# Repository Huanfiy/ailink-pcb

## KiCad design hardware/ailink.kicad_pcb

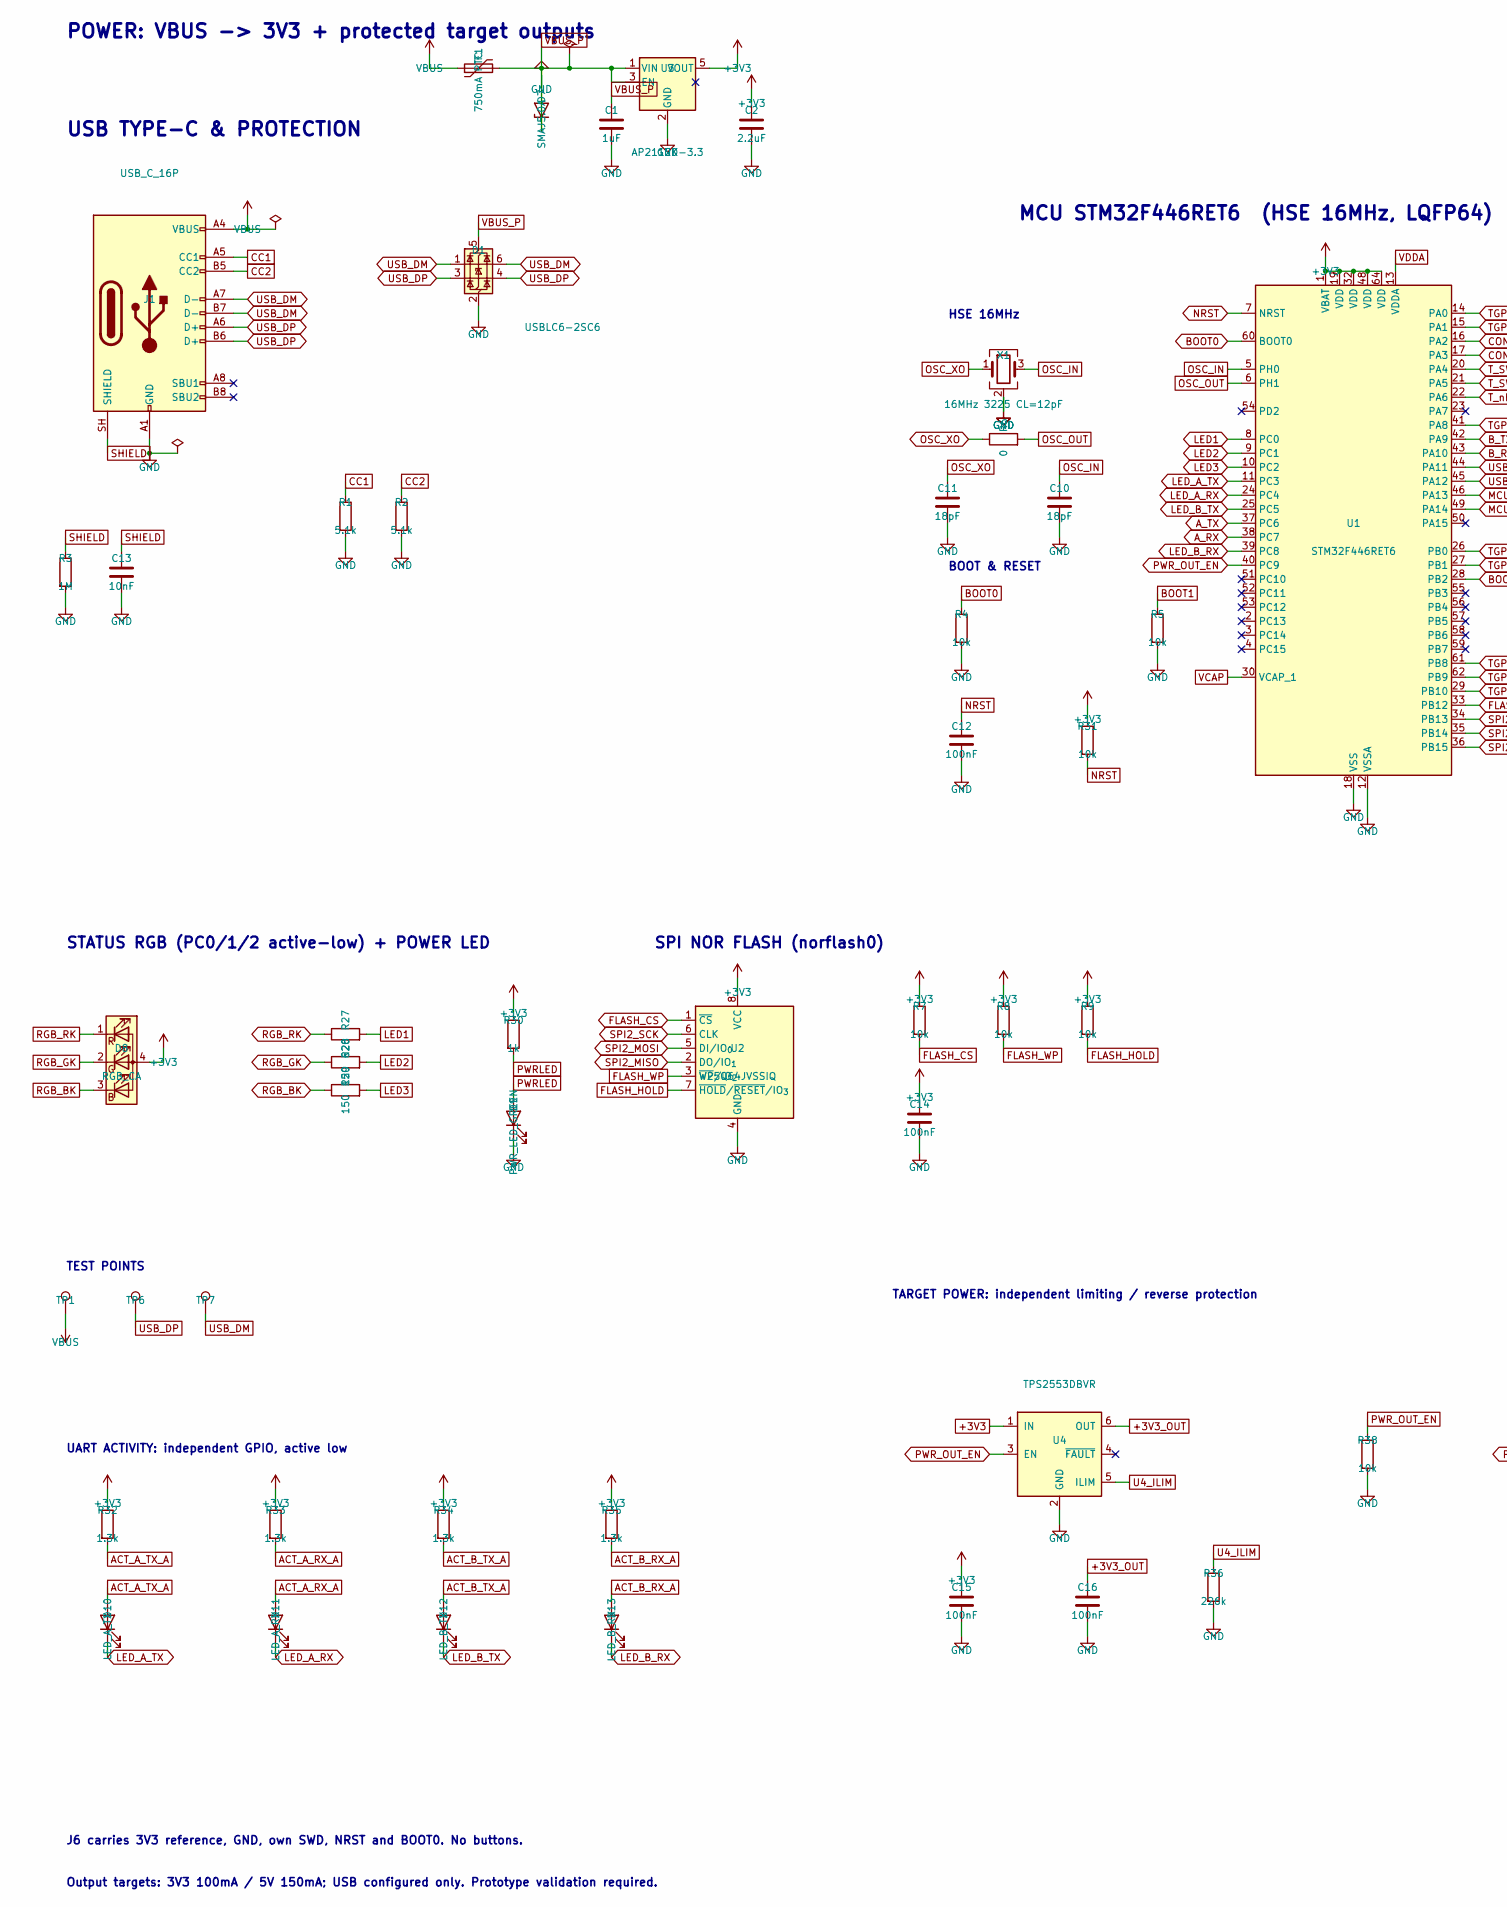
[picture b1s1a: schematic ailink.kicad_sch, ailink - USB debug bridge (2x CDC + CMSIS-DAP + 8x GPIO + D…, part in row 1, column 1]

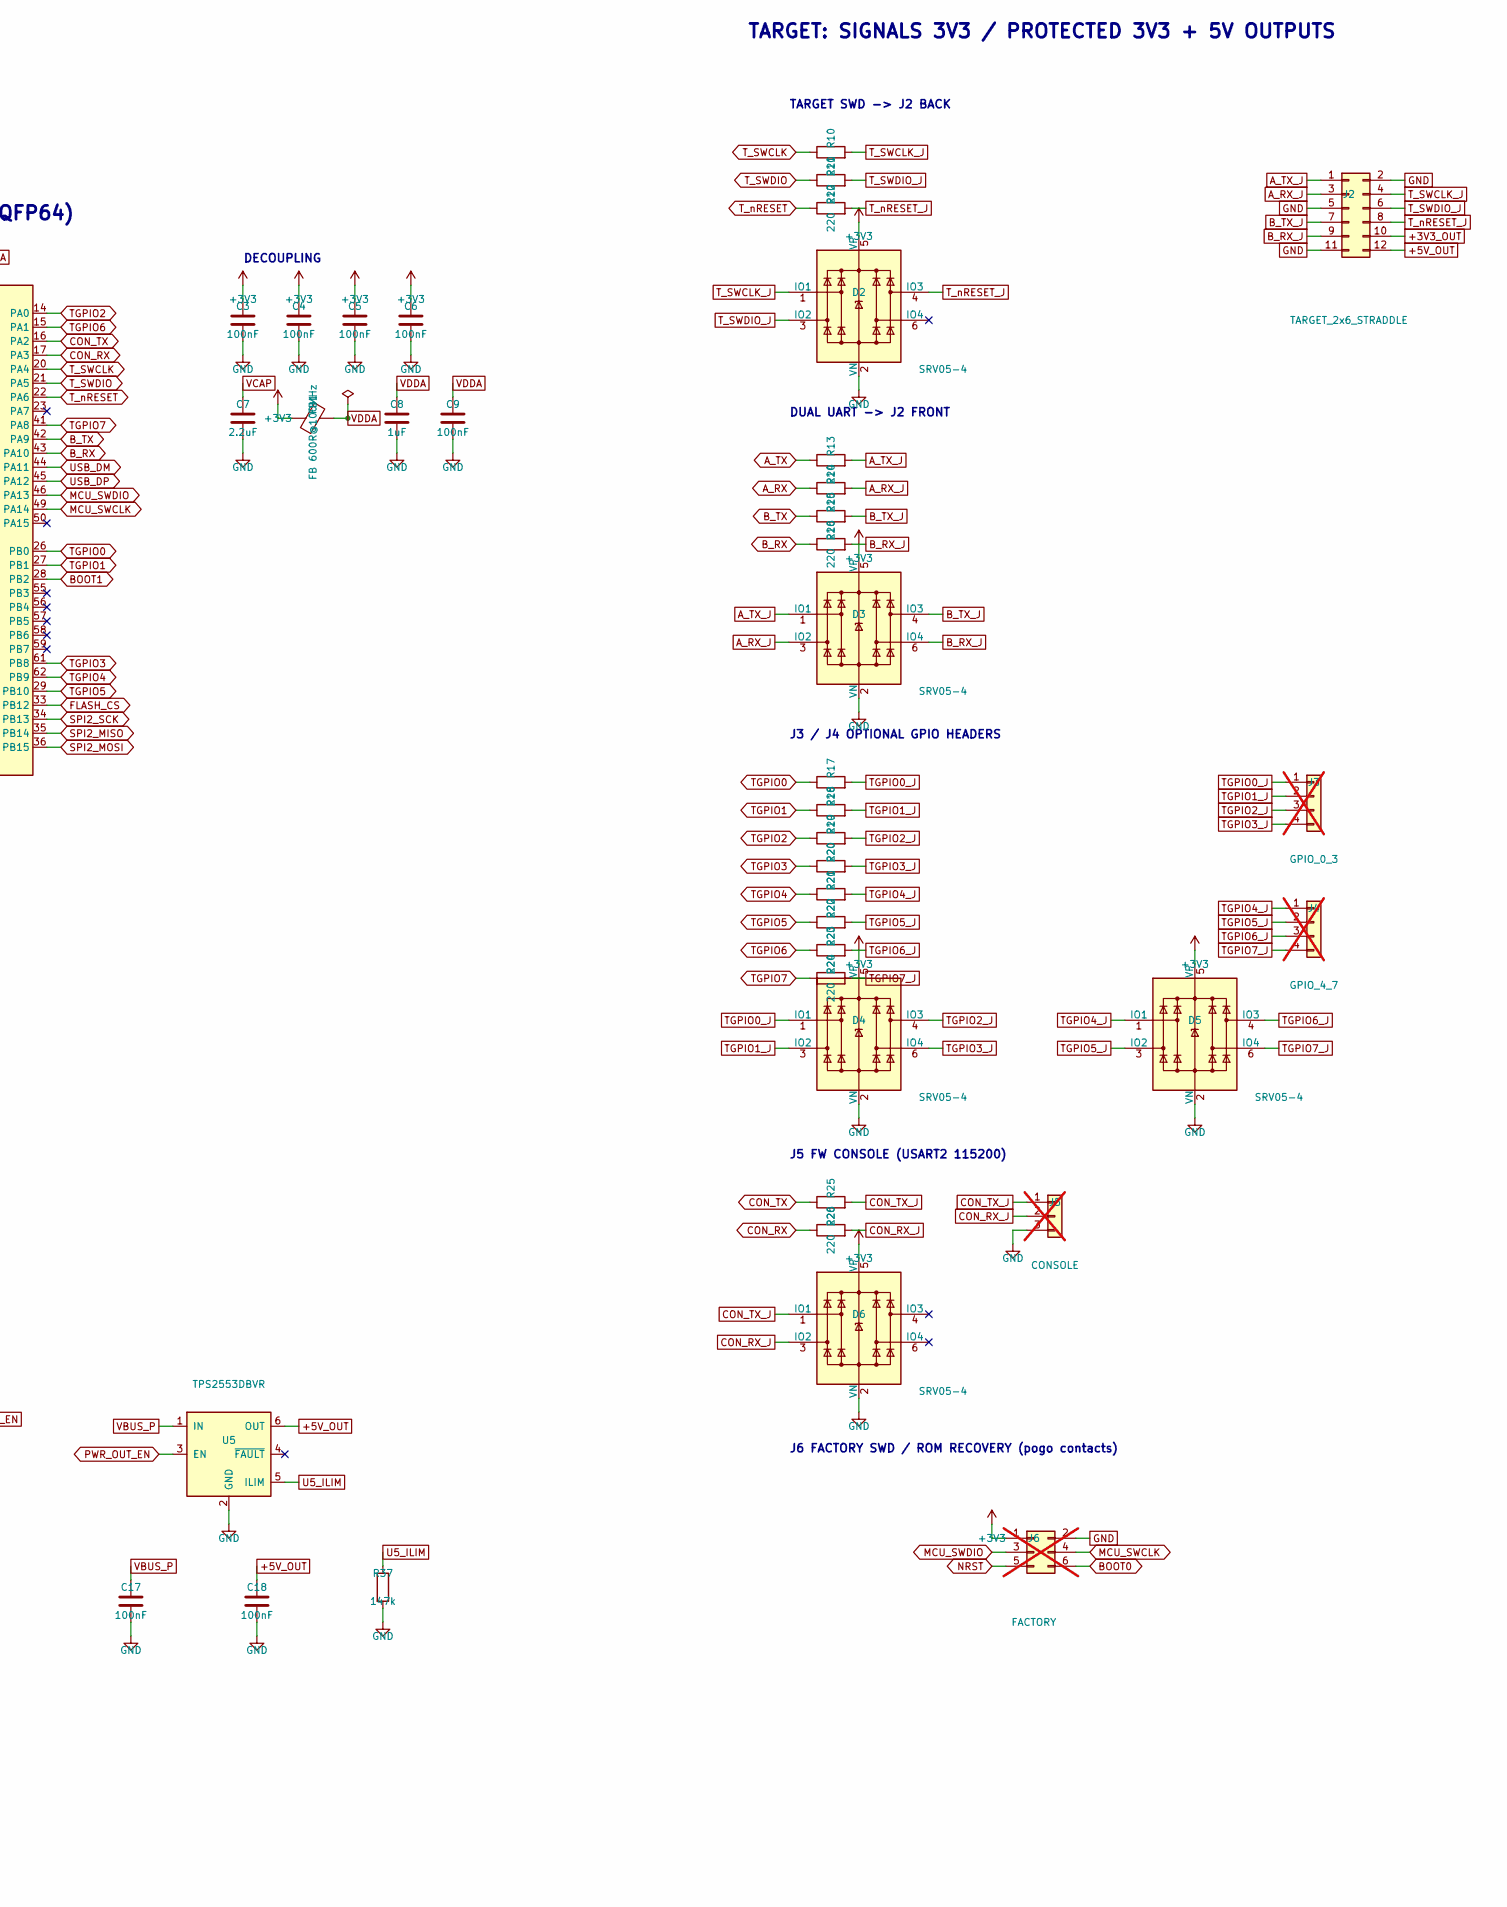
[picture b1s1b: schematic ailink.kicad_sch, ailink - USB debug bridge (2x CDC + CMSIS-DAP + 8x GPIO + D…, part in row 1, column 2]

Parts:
C1, C8: 1uF; Product_C_0603_1608Metric; MPN CL10A105KA8NNNC
C2, C7: 2.2uF; Product_C_0603_1608Metric; MPN CL10A225KA8NNNC
C3, C4, C5, C6, C9, C12, C14, C15, C16, C17, C18: 100nF; Product_C_0402_1005Metric; MPN CC0402KRX7R7BB104
C10, C11: 18pF; Product_C_0603_1608Metric; MPN C1608C0G1H180J
C13: 10nF; Product_C_0603_1608Metric; MPN CC0603KRX7R9BB103
D1: USBLC6-2SC6; Product_SOT-23-6; MPN USBLC6-2SC6
D2, D3, D4, D5, D6: SRV05-4; Product_SOT-23-6; MPN SRV05-4.TCT
D7: SMAJ5.0A; Product_D_SMA; MPN SMAJ5.0A
D8: RGB_CA; Product_LED_RGB_1210; MPN FM-B3227RGBA-HG
D9: PWR_LED_GREEN; Product_LED_0603_1608Metric; MPN KT-0603G
D10: LED_A_TX; Product_LED_0603_1608Metric; MPN LTST-C190KFKT
D11: LED_A_RX; Product_LED_0603_1608Metric; MPN LTST-C190KGKT
D12: LED_B_TX; Product_LED_0603_1608Metric; MPN LTST-C190KFKT
D13: LED_B_RX; Product_LED_0603_1608Metric; MPN LTST-C190KGKT
F1: 750mA PTC; Product_Fuse_1206_3216Metric; MPN 0ZCJ0075FF2E
FB1: FB 600R@100MHz; Product_L_0603_1608Metric; MPN BLM18AG601SN1D
J1: USB_C_16P; Product_USB_C_Receptacle_HRO_TYPE-C-31-M-12; MPN HRO TYPE-C-31-M-12
J2: TARGET_2x6_STRADDLE; Header_2x06_P2.54mm_Straddle; MPN TSW-106-07-L-D
J3: GPIO_0_3; Product_PinHeader_1x04_P2.54mm_Vertical; MPN PinHeader 1x4 2.54 直针; not fitted
J4: GPIO_4_7; Product_PinHeader_1x04_P2.54mm_Vertical; MPN PinHeader 1x4 2.54 直针; not fitted
J5: CONSOLE; Console_1x03_P1.27mm; MPN PCB contacts; not fitted
J6: FACTORY; Service_2x03_P1.27mm; MPN PCB contacts; not fitted
R1, R2: 5.1k; Product_R_0402_1005Metric; MPN RC0402FR-075K1L
R3: 1M; Product_R_0402_1005Metric; MPN RC0402JR-071ML
R4, R5, R7, R8, R9, R31, R38: 10k; Product_R_0402_1005Metric; MPN RC0402JR-0710KL
R6: 0; Product_R_0402_1005Metric; MPN RC0402JR-070RL
R10, R11, R12, R13, R14, R15, R16, R17, R18, R19, R20, R21, R22, R23, R24, R25, R26: 220; Product_R_0402_1005Metric; MPN RC0402FR-07220RL
R27: 620; Product_R_0402_1005Metric; MPN RC0402JR-07620RL
R28, R29: 150; Product_R_0402_1005Metric; MPN RC0402JR-07150RL
R30: 1k; Product_R_0402_1005Metric; MPN RC0402JR-071KL
R32, R33, R34, R35: 1.3k; Product_R_0402_1005Metric; MPN RC0402FR-071K3L
R36: 226k; Product_R_0402_1005Metric; MPN RC0402FR-07226KL
R37: 147k; Product_R_0402_1005Metric; MPN RC0402FR-07147KL
TP1: VBUS; Product_TestPoint_Pad_D1.0mm
TP6: USB_DP; Product_TestPoint_Pad_D1.0mm
TP7: USB_DM; Product_TestPoint_Pad_D1.0mm
U1: STM32F446RET6; Product_LQFP-64_10x10mm_P0.5mm; MPN STM32F446RET6
U2: W25Q64JVSSIQ; Product_SOIC-8_5.3x5.3mm_P1.27mm; MPN W25Q64JVSSIQ
U3: AP2112K-3.3; Product_SOT-23-5; MPN AP2112K-3.3TRG1
U4, U5: TPS2553DBVR; Product_SOT-23-6; MPN TPS2553DBVR
X1: 16MHz 3225 CL=12pF; Product_Crystal_SMD_3225-4Pin_3.2x2.5mm; MPN YSX321SL-16MHz或TXC 7V等效

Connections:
+3V3_OUT: C16.1, J2.10, U4.6 (OUT)
+5V_OUT: C18.1, J2.12, U5.6 (OUT)
ACT_A_RX_A: D11.2 (A), R33.2
ACT_A_TX_A: D10.2 (A), R32.2
ACT_B_RX_A: D13.2 (A), R35.2
ACT_B_TX_A: D12.2 (A), R34.2
A_RX: R14.1, U1.38 (PC7)
A_RX_J: D3.3 (IO2), J2.3, R14.2
A_TX: R13.1, U1.37 (PC6)
A_TX_J: D3.1 (IO1), J2.1, R13.2
BOOT0: J6.6, R4.1, U1.60 (BOOT0)
BOOT1: R5.1, U1.28 (PB2)
B_RX: R16.1, U1.43 (PA10)
B_TX: R15.1, U1.42 (PA9)
B_TX_J: D3.4 (IO3), J2.7, R15.2
CC1: J1.A5 (CC1), R1.1
CC2: J1.B5 (CC2), R2.1
CON_RX: R26.1, U1.17 (PA3)
CON_RX_J: D6.3 (IO2), J5.2, R26.2
CON_TX: R25.1, U1.16 (PA2)
CON_TX_J: D6.1 (IO1), J5.1, R25.2
FLASH_CS: R7.2, U1.33 (PB12), U2.1 (~CS)
FLASH_HOLD: R9.2, U2.7 (~HOLD/~RESET/IO_{3})
FLASH_WP: R8.2, U2.3 (~WP/IO_{2})
LED1: R27.2, U1.8 (PC0)
LED2: R28.2, U1.9 (PC1)
LED3: R29.2, U1.10 (PC2)
LED_A_RX: D11.1 (K), U1.24 (PC4)
LED_A_TX: D10.1 (K), U1.11 (PC3)
LED_B_RX: D13.1 (K), U1.39 (PC8)
LED_B_TX: D12.1 (K), U1.25 (PC5)
MCU_SWCLK: J6.4, U1.49 (PA14)
MCU_SWDIO: J6.3, U1.46 (PA13)
NRST: C12.1, J6.5, R31.2, U1.7 (NRST)
OSC_IN: C10.1, U1.5 (PH0), X1.3
OSC_OUT: R6.2, U1.6 (PH1)
OSC_XO: C11.1, R6.1, X1.1
PWRLED: D9.2 (A), R30.2
PWR_OUT_EN: R38.1, U1.40 (PC9), U4.3 (EN), U5.3 (EN)
RGB_BK: D8.3 (BK), R29.1
RGB_GK: D8.2 (GK), R28.1
RGB_RK: D8.1 (RK), R27.1
SHIELD: C13.1, J1.SH (SHIELD), R3.1
SPI2_MISO: U1.35 (PB14), U2.2 (DO/IO_{1})
SPI2_MOSI: U1.36 (PB15), U2.5 (DI/IO_{0})
SPI2_SCK: U1.34 (PB13), U2.6 (CLK)
TGPIO0: R17.1, U1.26 (PB0)
TGPIO0_J: D4.1 (IO1), J3.1, R17.2
TGPIO1: R18.1, U1.27 (PB1)
TGPIO1_J: D4.3 (IO2), J3.2, R18.2
TGPIO2: R19.1, U1.14 (PA0)
TGPIO2_J: D4.4 (IO3), J3.3, R19.2
TGPIO3: R20.1, U1.61 (PB8)
TGPIO3_J: D4.6 (IO4), J3.4, R20.2
TGPIO4: R21.1, U1.62 (PB9)
TGPIO4_J: D5.1 (IO1), J4.1, R21.2
TGPIO5: R22.1, U1.29 (PB10)
TGPIO5_J: D5.3 (IO2), J4.2, R22.2
TGPIO6: R23.1, U1.15 (PA1)
TGPIO7: R24.1, U1.41 (PA8)
TGPIO7_J: D5.6 (IO4), J4.4, R24.2
T_SWCLK: R10.1, U1.20 (PA4)
T_SWCLK_J: D2.1 (IO1), J2.4, R10.2
T_SWDIO: R11.1, U1.21 (PA5)
T_SWDIO_J: D2.3 (IO2), J2.6, R11.2
T_nRESET: R12.1, U1.22 (PA6)
T_nRESET_J: D2.4 (IO3), J2.8, R12.2
U4_ILIM: R36.1, U4.5 (ILIM)
U5_ILIM: R37.1, U5.5 (ILIM)
USB_DM: D1.1 (I/O1), D1.6 (I/O1), J1.A7 (D-), J1.B7 (D-), TP7.1, U1.44 (PA11)
USB_DP: D1.3 (I/O2), D1.4 (I/O2), J1.A6 (D+), J1.B6 (D+), TP6.1, U1.45 (PA12)
VBUS: F1.1, J1.A4 (VBUS), J1.A9 (VBUS), J1.B4 (VBUS), J1.B9 (VBUS), TP1.1
VCAP: C7.1, U1.30 (VCAP_1)
VDDA: C8.1, C9.1, FB1.2, U1.13 (VDDA)

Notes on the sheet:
USB TYPE-C & PROTECTION
POWER: VBUS -> 3V3 + protected target outputs
MCU STM32F446RET6 (HSE 16MHz, LQFP64)
DECOUPLING
HSE 16MHz
BOOT & RESET
SPI NOR FLASH (norflash0)
STATUS RGB (PC0/1/2 active-low) + POWER LED
TARGET: SIGNALS 3V3 / PROTECTED 3V3 + 5V OUTPUTS
TARGET SWD -> J2 BACK
DUAL UART -> J2 FRONT
J3 / J4 OPTIONAL GPIO HEADERS
J5 FW CONSOLE (USART2 115200)
J6 FACTORY SWD / ROM RECOVERY (pogo contacts)
TEST POINTS
UART ACTIVITY: independent GPIO, active low
TARGET POWER: independent limiting / reverse protection
J6 carries 3V3 reference, GND, own SWD, NRST and BOOT0. No buttons.
Output targets: 3V3 100mA / 5V 150mA; USB configured only. Prototype validation required.

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
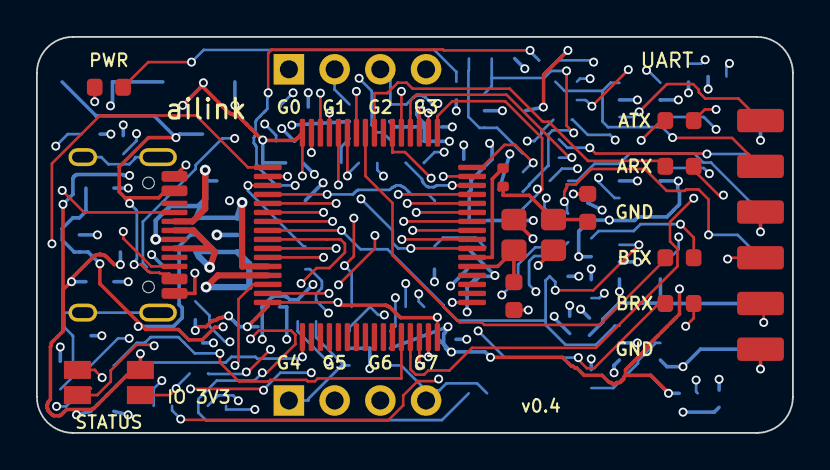
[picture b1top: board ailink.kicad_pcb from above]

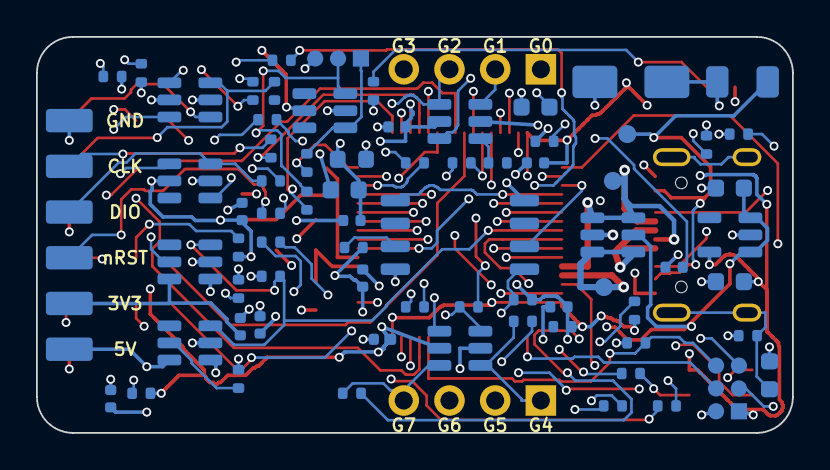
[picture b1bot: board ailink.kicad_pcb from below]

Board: 4 copper layers, 42.0 x 22.0 mm, 86 parts (71 on the bottom side), 79 nets.

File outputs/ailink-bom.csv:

"Refs","Value","Footprint","MPN","Spec","Qty","DNP"
"C1,C8","1uF","Capacitor_SMD:C_0603_1608Metric","CL10A105KA8NNNC","0603 X7R/X5R 25V","2",""
"C2","2.2uF","Capacitor_SMD:C_0603_1608Metric","CL10A225KA8NNNC","0603 X7R/X5R 25V","1",""
"C3-C6,C9,C12,C14","100nF","Capacitor_SMD:C_0603_1608Metric","CC0603KRX7R8BB104","0603 X7R/X5R 25V","7",""
"C7","2.2uF","Capacitor_SMD:C_0603_1608Metric","CL10A225KA8NNNC","0603 X7R/X5R 25V 低ESR（VCAP）","1",""
"C10,C11","18pF","Capacitor_SMD:C_0603_1608Metric","C1608C0G1H180J","0603 C0G/NP0 50V","2",""
"C13","10nF","Capacitor_SMD:C_0603_1608Metric","CC0603KRX7R9BB103","0603 X7R 50V","1",""
"D1","USBLC6-2SC6","Package_TO_SOT_SMD:SOT-23-6","USBLC6-2SC6","SOT-23-6 超低容USB ESD","1",""
"D2-D6","SRV05-4","Package_TO_SOT_SMD:SOT-23-6","SRV05-4.TCT","SOT-23-6 4ch ESD, C~3pF/线","5",""
"D7","SMAJ5.0A","Diode_SMD:D_SMA","SMAJ5.0A","SMA 单向TVS 5V/400W","1",""
"D8","RGB_CA","LED_SMD:LED_RGB_1210","FM-B3227RGBA-HG","国星1210(3227)共阳RGB,装配前按规格书核对1-4脚序","1",""
"D9","PWR_LED_GREEN","LED_SMD:LED_0603_1608Metric","KT-0603G","0603绿色,VF~3V@2mA","1",""
"F1","350mA PTC","Fuse:Fuse_1206_3216Metric","0ZCJ0035FF2E","1206 PTC 350mA/6V","1",""
"FB1","FB 600R@100MHz","Inductor_SMD:L_0603_1608Metric","BLM18AG601SN1D","0603 600R@100MHz","1",""
"H1-H4","M2","MountingHole:MountingHole_2.2mm_M2","","","4",""
"J1","USB_C_16P","Connector_USB:USB_C_Receptacle_HRO_TYPE-C-31-M-12","HRO TYPE-C-31-M-12","USB-C 16P USB2.0","1",""
"J2","SWD_OUT","Connector_PinHeader_2.54mm:PinHeader_1x04_P2.54mm_Vertical","PinHeader 1x4 2.54 直针","PinHeader 1x4 2.54 直针","1",""
"J3","UART_AB","Connector_PinHeader_2.54mm:PinHeader_2x03_P2.54mm_Vertical","PinHeader 2x3 2.54 直针","PinHeader 2x3 2.54 直针","1",""
"J4","GPIO_0_7","Connector_PinHeader_2.54mm:PinHeader_2x05_P2.54mm_Vertical","PinHeader 2x5 2.54 直针","PinHeader 2x5 2.54 直针","1",""
"J5","CONSOLE","Connector_PinHeader_2.54mm:PinHeader_1x03_P2.54mm_Vertical","PinHeader 1x3 2.54 直针","PinHeader 1x3 2.54 直针","1",""
"R1,R2","5.1k","Resistor_SMD:R_0603_1608Metric","RC0603FR-075K1L","0603 ±1%","2",""
"R3","1M","Resistor_SMD:R_0603_1608Metric","RC0603JR-071ML","0603 ±5%","1",""
"R4,R5,R7-R9","10k","Resistor_SMD:R_0603_1608Metric","RC0603JR-0710KL","0603 ±5%","5",""
"R6","0","Resistor_SMD:R_0603_1608Metric","RC0603JR-070RL","0603 0Ω","1",""
"R10-R26","220","Resistor_SMD:R_0603_1608Metric","RC0603FR-07220RL","0603 ±1%","17",""
"R27","620","Resistor_SMD:R_0603_1608Metric","RC0603JR-07620RL","0603 ±5%","1",""
"R28,R29","150","Resistor_SMD:R_0603_1608Metric","RC0603JR-07150RL","0603 ±5%","2",""
"R30","1k","Resistor_SMD:R_0603_1608Metric","RC0603JR-071KL","0603 ±5%","1",""
"SW1","S_BOOT","Button_Switch_SMD:SW_SPST_PTS810","C&K PTS810SJK250SMTRLFS","4.2x3.2轻触","1",""
"SW2","S_RST","Button_Switch_SMD:SW_SPST_PTS810","C&K PTS810SJK250SMTRLFS","4.2x3.2轻触","1",""
"TP1","VBUS","TestPoint:TestPoint_Pad_D1.5mm","","","1",""
"TP2","+3V3","TestPoint:TestPoint_Pad_D1.5mm","","","1",""
"TP3","GND","TestPoint:TestPoint_Pad_D1.5mm","","","1",""
"TP4","NRST","TestPoint:TestPoint_Pad_D1.5mm","","","1",""
"TP5","BOOT0","TestPoint:TestPoint_Pad_D1.5mm","","","1",""
"TP6","USB_DP","TestPoint:TestPoint_Pad_D1.5mm","","","1",""
"TP7","USB_DM","TestPoint:TestPoint_Pad_D1.5mm","","","1",""
"U1","STM32F446RET6","Package_QFP:LQFP-64_10x10mm_P0.5mm","STM32F446RET6","LQFP64","1",""
"U2","W25Q64JVSSIQ","Package_SO:SOIC-8_5.3x5.3mm_P1.27mm","W25Q64JVSSIQ","SOIC-8 208mil","1",""
"U3","AP2112K-3.3","Package_TO_SOT_SMD:SOT-23-5","AP2112K-3.3TRG1","SOT-23-5 600mA","1",""
"X1","16MHz 3225 CL=12pF","Crystal:Crystal_SMD_3225-4Pin_3.2x2.5mm","YSX321SL-16MHz或TXC 7V等效","3225 16MHz ±10ppm CL=12pF","1",""

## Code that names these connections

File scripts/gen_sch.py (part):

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    auto_label(j1, "A5", "CC1", shape="passive")
    auto_label(j1, "B5", "CC2", shape="passive")
    # D+/D- (per-pin labels; single net through USBLC6)
    auto_label(j1, "A7", "USB_DM", shape="bidirectional")
    auto_label(j1, "B7", "USB_DM", shape="bidirectional")
    auto_label(j1, "A6", "USB_DP", shape="bidirectional")
    auto_label(j1, "B6", "USB_DP", shape="bidirectional")
    nc(j1, "A8")
    nc(j1, "B8")
    # GND (stacked) + PWR_FLAG
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    d.pwr_flag(round(pg1[0] + g(4), 4), pg1[1])
    d.junction(pg1)
    # shield
    auto_label(j1, "SH", "SHIELD", shape="passive")

    r1 = vert_rc("R1", S_R, g(64), g(88), "5.1k", FP["R"], "CC1")
    r2 = vert_rc("R2", S_R, g(72), g(88), "5.1k", FP["R"], "CC2")
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    d1 = d.place("D1", S_USBLC, g(83), g(52), value="USBLC6-2SC6",
                 footprint=FP["SOT236"], value_at=(g(95), g(61)),
                 props=PARTS["D1"])
    auto_label(d1, "1", "USB_DM", shape="bidirectional")
    auto_label(d1, "6", "USB_DM", shape="bidirectional")
    auto_label(d1, "3", "USB_DP", shape="bidirectional")
    auto_label(d1, "4", "USB_DP", shape="bidirectional")
    auto_label(d1, "5", "VBUS_P", shape="passive")
    auto_gnd(d1, "2")

    # ================= power =================
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    # node VBUS_P
    node = (g(92), g(y_pw))
    d.wire(f1.pin("2"), node)
    d.label_right("VBUS_P", (g(92), g(y_pw - 4)), shape="passive")
    d.wire(node, (g(92), g(y_pw - 4)))
    d.pwr_flag(g(96), g(y_pw - 2))
    d.wire(node, (g(96), g(y_pw)))
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    d.wire(pvssa, (pvssa[0], round(pvssa[1] + g(4), 4)))
    d.power("GND", pvssa[0], round(pvssa[1] + g(4), 4))
    # VCAP
    auto_label(u1, "30", "VCAP", shape="passive")
    # left-side signals
    auto_label(u1, "7", "NRST")          # NRST
    auto_label(u1, "60", "BOOT0")        # BOOT0
    auto_label(u1, "5", "OSC_IN", shape="passive")
    auto_label(u1, "6", "OSC_OUT", shape="passive")
    auto_label(u1, "8", "LED1")
    auto_label(u1, "9", "LED2")
    auto_label(u1, "10", "LED3")
    auto_label(u1, "37", "A_TX")
    auto_label(u1, "38", "A_RX")
    for pin, net in (("11", "LED_A_TX"), ("24", "LED_A_RX"),
                     ("25", "LED_B_TX"), ("39", "LED_B_RX"), ("40", "PWR_OUT_EN")):
        auto_label(u1, pin, net)
    # right-side signals
    right = {
        "14": "TGPIO2", "15": "TGPIO6", "16": "CON_TX", "17": "CON_RX",
        "20": "T_SWCLK", "21": "T_SWDIO", "22": "T_nRESET",
        "41": "TGPIO7", "42": "B_TX", "43": "B_RX",
        "44": "USB_DM", "45": "USB_DP",
        "46": "MCU_SWDIO", "49": "MCU_SWCLK",
        "26": "TGPIO0", "27": "TGPIO1", "28": "BOOT1",
        "61": "TGPIO3", "62": "TGPIO4", "29": "TGPIO5",
        "33": "FLASH_CS", "34": "SPI2_SCK", "35": "SPI2_MISO",
        "36": "SPI2_MOSI",
    }
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    x1 = d.place("X1", S_XTAL, g(158), g(67), value="16MHz 3225 CL=12pF",
                 footprint=FP["XTAL"], value_at=(g(158), g(72)),
                 props=PARTS["X1"])
    auto_label(x1, "1", "OSC_XO", shape="passive")
    auto_label(x1, "3", "OSC_IN", shape="passive")
    auto_gnd(x1, "2")
    auto_gnd(x1, "4")
    r6 = series_r("R6", g(158), g(77), "OSC_XO", "OSC_OUT", value="0")
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    d.text("SPI NOR FLASH (norflash0)", g(108), g(150), size=2.0)
    u2 = d.place("U2", S_W25, g(120), g(166), value="W25Q64JVSSIQ",
                 footprint=FP["FLASH"], props=PARTS["U2"])
    auto_label(u2, "1", "FLASH_CS")
    auto_label(u2, "2", "SPI2_MISO")
    auto_label(u2, "5", "SPI2_MOSI")
    auto_label(u2, "6", "SPI2_SCK")
    auto_label(u2, "3", "FLASH_WP", shape="passive")
    auto_label(u2, "7", "FLASH_HOLD", shape="passive")
    auto_pwr(u2, "8", net="+3V3")
    auto_gnd(u2, "4")
    r7 = vert_rc("R7", S_R, g(146), g(160), "10k", FP["R"], "+3V3",
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    c14 = vert_rc("C14", S_C, g(146), g(174), "100nF", "Capacitor_SMD:C_0402_1005Metric", "+3V3")

    # ================= LEDs =================
    d.text("STATUS RGB (PC0/1/2 active-low) + POWER LED", g(24), g(150),
           size=2.0)
    d8 = d.place("D8", S_RGB, g(32), g(166), value="RGB_CA",
                 footprint=FP["RGB"], props=PARTS["D8"])
    auto_pwr(d8, "4", net="+3V3")
    auto_label(d8, "1", "RGB_RK", shape="passive")
    auto_label(d8, "2", "RGB_GK", shape="passive")
    auto_label(d8, "3", "RGB_BK", shape="passive")
    r27 = series_r("R27", g(64), g(162), "RGB_RK", "LED1", value="620")
    r28 = series_r("R28", g(64), g(166), "RGB_GK", "LED2", value="150")
    r29 = series_r("R29", g(64), g(170), "RGB_BK", "LED3", value="150")
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    d9 = d.place("D9", S_LED, g(88), g(174), rot=90, value="PWR_LED_GREEN",
                 footprint=FP["LED"], props=PARTS["D9"])
    # LED: pin1=K, pin2=A ; rot90 -> A up, K down
    auto_label(d9, "2", "PWRLED", shape="passive")
    auto_gnd(d9, "1")

    # ================= target interfaces =================
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    d2 = d.place("D2", S_SRV, g(340), g(58), value="SRV05-4",
                 footprint=FP["SOT236"], value_at=(g(352), g(67)),
                 props=PARTS["D2"])
    auto_label(d2, "1", "T_SWCLK_J", shape="passive")
    auto_label(d2, "3", "T_SWDIO_J", shape="passive")
    auto_label(d2, "4", "T_nRESET_J", shape="passive")
    nc(d2, "6")
    auto_pwr(d2, "5", net="+3V3")
    auto_gnd(d2, "2")
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    d3 = d.place("D3", S_SRV, g(340), g(104), value="SRV05-4",
                 footprint=FP["SOT236"], value_at=(g(352), g(113)),
                 props=PARTS["D3"])
    auto_label(d3, "1", "A_TX_J", shape="passive")
    auto_label(d3, "3", "A_RX_J", shape="passive")
    auto_label(d3, "4", "B_TX_J", shape="passive")
    auto_label(d3, "6", "B_RX_J", shape="passive")
    auto_pwr(d3, "5", net="+3V3")
    auto_gnd(d3, "2")

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    j5 = d.place("J5", S_C1X3, g(368), g(188), value="CONSOLE",
                 footprint=FP["CONSOLE"], dnp=True, in_bom=False, value_at=(g(368), g(195)),
                 props=PARTS["J5"])
    auto_label(j5, "1", "CON_TX_J", shape="passive")
    auto_label(j5, "2", "CON_RX_J", shape="passive")
    auto_gnd(j5, "3")
    d6 = d.place("D6", S_SRV, g(340), g(204), value="SRV05-4",
                 footprint=FP["SOT236"], value_at=(g(352), g(213)),
                 props=PARTS["D6"])
    auto_label(d6, "1", "CON_TX_J", shape="passive")
    auto_label(d6, "3", "CON_RX_J", shape="passive")
    nc(d6, "4")
    nc(d6, "6")
    auto_pwr(d6, "5", net="+3V3")
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                 value_at=(g(365), g(246)))
    auto_pwr(j6, "1", net="+3V3")
    auto_label(j6, "2", "GND", shape="passive")
    for pin, net in (("3", "MCU_SWDIO"), ("4", "MCU_SWCLK"), ("5", "NRST"), ("6", "BOOT0")):
        auto_label(j6, pin, net)

    # ================= test points =================
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                     value_at=(g(x), g(212)))
        auto_label(sw, "1", supply, shape="passive")
        auto_gnd(sw, "2")
        auto_label(sw, "3", "PWR_OUT_EN")
        nc(sw, "4")  # Autonomous current limiting and thermal auto-retry.
        auto_label(sw, "5", f"{ref}_ILIM", shape="passive")
        auto_label(sw, "6", output, shape="passive")
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
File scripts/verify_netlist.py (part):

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
    # ---- product.md §5.1: MCU pin table ----
    pinmap = {
        "14": "TGPIO2", "15": "TGPIO6", "16": "CON_TX", "17": "CON_RX",
        "20": "T_SWCLK", "21": "T_SWDIO", "22": "T_nRESET",
        "41": "TGPIO7", "42": "B_TX", "43": "B_RX",
        "44": "USB_DM", "45": "USB_DP",
        "46": "MCU_SWDIO", "49": "MCU_SWCLK",
        "26": "TGPIO0", "27": "TGPIO1", "28": "BOOT1",
        "61": "TGPIO3", "62": "TGPIO4", "29": "TGPIO5",
        "33": "FLASH_CS", "34": "SPI2_SCK", "35": "SPI2_MISO",
        "36": "SPI2_MOSI",
        "8": "LED1", "9": "LED2", "10": "LED3",
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        ("A_RX", "R14", "A_RX_J", None, "D3-3"),
        ("B_TX", "R15", "B_TX_J", None, "D3-4"),
        ("B_RX", "R16", "B_RX_J", None, "D3-6"),
        ("TGPIO0", "R17", "TGPIO0_J", "J3-1", "D4-1"),
        ("TGPIO1", "R18", "TGPIO1_J", "J3-2", "D4-3"),
        ("TGPIO2", "R19", "TGPIO2_J", "J3-3", "D4-4"),
        ("TGPIO3", "R20", "TGPIO3_J", "J3-4", "D4-6"),
        ("TGPIO4", "R21", "TGPIO4_J", "J4-1", "D5-1"),
        ("TGPIO5", "R22", "TGPIO5_J", "J4-2", "D5-3"),
        ("TGPIO6", "R23", "TGPIO6_J", "J4-3", "D5-4"),
        ("TGPIO7", "R24", "TGPIO7_J", "J4-4", "D5-6"),
        ("CON_TX", "R25", "CON_TX_J", "J5-1", "D6-1"),
        ("CON_RX", "R26", "CON_RX_J", "J5-2", "D6-3"),
    ]
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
